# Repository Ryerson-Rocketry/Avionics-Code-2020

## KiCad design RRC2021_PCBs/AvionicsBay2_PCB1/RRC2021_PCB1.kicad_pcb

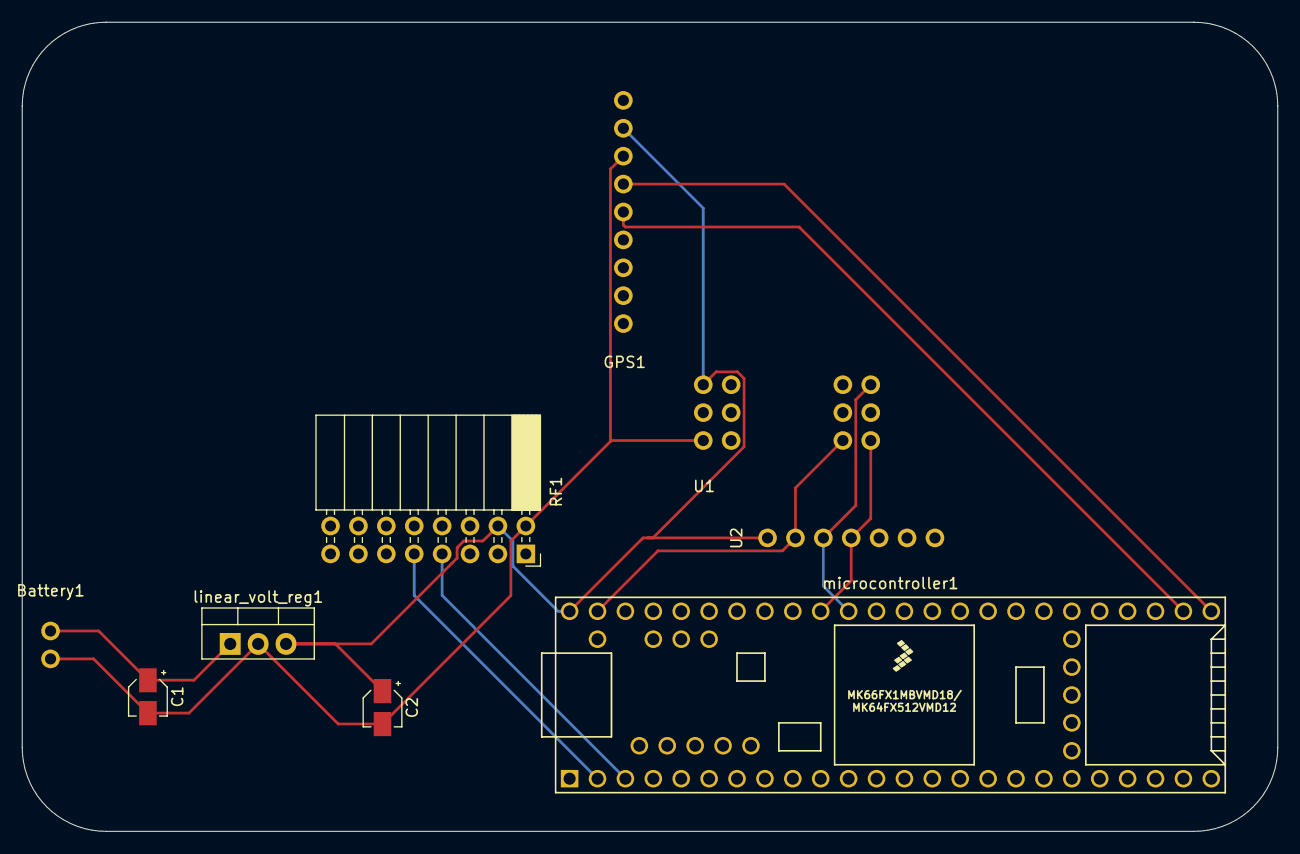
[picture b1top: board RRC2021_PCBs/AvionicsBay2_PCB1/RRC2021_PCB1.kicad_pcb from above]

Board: 2 copper layers, 114.3 x 73.7 mm, 9 parts (0 on the bottom side), 10 nets.

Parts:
Battery1: 9V; 1x02
C1: 0.33uF; CP_Elec_3x5.3
C2: 0.1uF; CP_Elec_3x5.3
GPS1: AULT_GPS; 1x09
RF1: RFD900+; PinSocket_2x08_P2.54mm_Horizontal
U1: ADXL357z; ADXLZ
U2: MS5611; 1x07
linear_volt_reg1: LM7805_TO220; TO-220-3_Vertical
microcontroller1: Teensy3.6; Teensy35_36

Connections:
unnamed: Battery1.1, C1.1, linear_volt_reg1.1
unnamed: Battery1.2, C1.2, C2.2, GPS1.7, RF1.2, U1.6, linear_volt_reg1.2
unnamed: C2.1, GPS1.8, RF1.4, U1.5, U2.1, linear_volt_reg1.3, microcontroller1.53
unnamed: GPS1.5, microcontroller1.31
unnamed: GPS1.6, microcontroller1.30
unnamed: RF1.7, microcontroller1.3
unnamed: RF1.9, microcontroller1.2
unnamed: U1.1, U2.3, microcontroller1.43
unnamed: U1.3, U2.4, microcontroller1.44
unnamed: U1.4, U2.2, microcontroller1.52

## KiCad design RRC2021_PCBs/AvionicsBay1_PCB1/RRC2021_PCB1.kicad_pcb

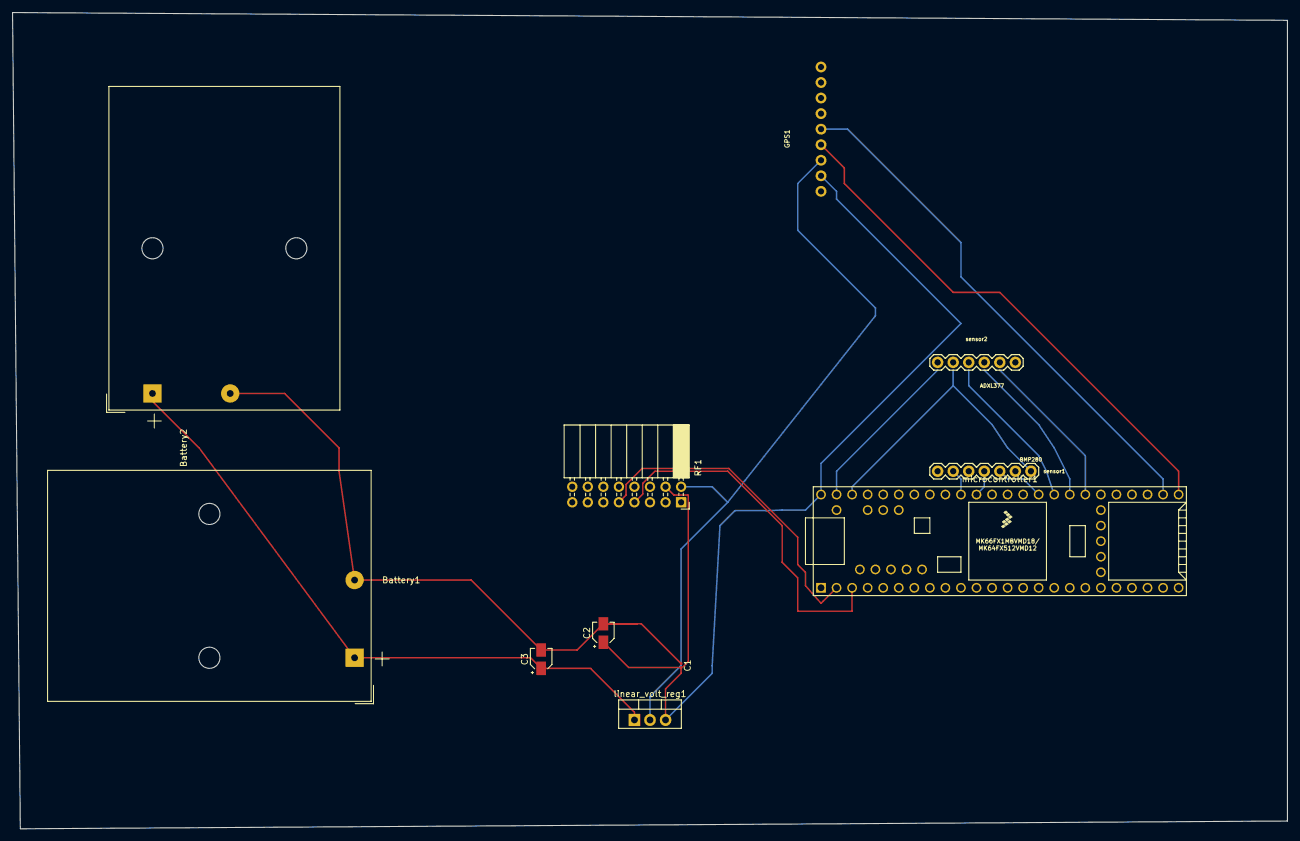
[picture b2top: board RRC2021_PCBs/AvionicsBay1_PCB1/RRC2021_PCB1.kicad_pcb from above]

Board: 2 copper layers, 208.3 x 133.3 mm, 11 parts (0 on the bottom side), 15 nets.

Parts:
Battery1, Battery2: 4.5V; BatteryHolder_Keystone_2479_3xAAA
C1: 0.1uF; C_0201_0603Metric
C2, C3: 10uF; CP_Elec_3x5.3
GPS1: AULT_GPS; 1X09_ROUND_70
RF1: RFD900+; PinSocket_2x08_P2.54mm_Horizontal
linear_volt_reg1: LM7805_TO220; TO-220-3_Vertical
microcontroller1: Teensy3.6; Teensy35_36
sensor1: BMP280; 1X07
sensor2: ADXL377; 1X06

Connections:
unnamed: Battery1.1, Battery2.1, C3.1, linear_volt_reg1.1
unnamed: Battery1.2, Battery2.2, C1.1, C2.2, C3.2, GPS1.7, RF1.2, linear_volt_reg1.2
unnamed: C1.2, C2.1, GPS1.8, RF1.4, linear_volt_reg1.3, microcontroller1.53
unnamed: GPS1.5, microcontroller1.31
unnamed: GPS1.6, microcontroller1.30
unnamed: RF1.7, microcontroller1.3
unnamed: RF1.9, microcontroller1.2
unnamed: microcontroller1.36, sensor2.5
unnamed: microcontroller1.37, sensor2.4
unnamed: microcontroller1.38, sensor2.3
unnamed: microcontroller1.39, sensor1.3
unnamed: microcontroller1.43, sensor1.4
unnamed: microcontroller1.44, sensor1.6
unnamed: microcontroller1.51, sensor1.1, sensor2.2
unnamed: microcontroller1.52, sensor2.1

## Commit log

2020-08-22 Create test
2020-09-05 Create Test
    Create folder
2020-10-02 oragnizing files
2020-10-05 gps issue was almost entirely fixed
2020-10-15 Added low pass filter code in comments, as it uses already in-use values.
2020-10-20 Deleted old acceleration filtering system and replaced with low pass filter
2020-10-26 Fixed bug in low pass filter
2021-02-07 updated gps part of code
2021-02-08 changed ADXL377 code a bit
2021-02-08 organizing files
2021-02-08 organizing and deleting files
2021-02-08 removing files
2021-02-16 Fixed GPS and accelerometer issues #5:
2021-02-16 #5: added 1st rough kicad PCB design for the 1st stage avionics bay
2021-02-16 #5: fixed pcb1 schematic
2021-02-17 #5: cleaned main code a bit, also fixed time counter and serial write issures
2021-02-24 #5: organized main code and fixed analog calibration value read to be +-1.8g with the goal being 0g for rest values
2021-03-11 #7 antenna link budget and simulation
2021-03-20 #5: fixed a few things with the analog reading, and added reading/writing to sd card code
2021-05-05 Create temp
2021-05-05 Create Temp2
2021-05-06 #5: added in and tweaked some stuff related to accelerometer
2021-05-19 #5 ADXL357Z sensor Added to PCB
2021-05-27 #5: edited/organized stuff
2021-05-28 #5: edited/deleted useless stuff for main code
2021-06-02 Delete Groundstation_GUI directory
    Moving to new repository
2021-06-08 #5: edited GPS from scratch code
2021-06-08 #5: updated main code + GPS code for both adafruit ultimate gps and gn220 GPS
2021-06-17 #5: updated GPS code from scratch + deleted/organized MainBayCode
2021-06-17 #5: cleaned up main code / made some SD card functions
2021-06-17 #5: updated main code
2021-06-17 #5: updated main code- sd card, bmp280, and bn220 gps integrated effectively
2021-07-14 update pcb
